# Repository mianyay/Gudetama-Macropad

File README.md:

# Gudetama-Macropad
A Gudetama-themed macropad designed using the Hackpad guide. It has 5 keys with a knob that adjusts the volume, an OLED Display, and 4 RGB LEDs.

Project: https://stardance.hackclub.com/projects/28602

## Features 
- 5x Keys
- 1x Rotary Encoder
- 1x 0.91" SSD1306 OLED, 128x32
- 4x SK6812 MINI-E rear-mount RGB LEDs
- 1x Transparent Acrylic (62mm x 34mm)
- Gudetama-themed silkscreen + engraved case!

## Key Map
| Type | Action |
| --- | --- |
| SW1 | Copy |
| SW2 | Paste |
| SW3 | Undo |
| SW4 | Redo |
| SW5 | Play/Pause |
| Knob (when pressed) | Mute |
| Knob (turned) | Volume adjusted up and down |

## Hardware
- **Microcontroller**: Seeed XIAO RP2040
- **PCB**: 80 x 115 mm, 2-layer, designed in KiCad
- **Case**: 3D-printed tray and frame, designed in Onshape
- **Transparent Window**: 3 mm clear acrylic (laser-cut)

## Firmware

Written in VS Code using CircuitPython + KMK. AI was used to help write some of the code.
- code.py - full firmware
- test_keys.py - buttons only to test wiring

## Repository Layout
- `/pcb` - KiCad schematic, PCB layout, and gerbers
- `/case` - STL files for the top frame, tray and knob
- `/firmware` - CircuitPython/KMK code

## Schematic

## PCB

## CAD

Link: https://cad.onshape.com/documents/9705477a2f20afdacdcfdba6/w/f3cf2669e06390f3bc4361ff/e/a85cb6eed9ad57064a269f1d?renderMode=0&uiState=6ad9a16c61fea2212d106cef

## BOM
- 1x Seeed XIAO RP2040
- 5x Cherry MX switches 
- 5x DSA blank keycaps
- 1x EC11E rotary encoder 
- 4x SK6812 MINI-E RGB LEDs 
- 1x 0.91" SSD1306 OLED display, 128x32
- 6x M3x16mm SHCS bolts
- 6x M3x5mx4mm heatset inserts
- 1x PCB (80 x 115 mm)
- 3x 3D-printed parts (top frame, bottom tray, knob)
- 1x laser-cut part (3 mm clear acrylic window)

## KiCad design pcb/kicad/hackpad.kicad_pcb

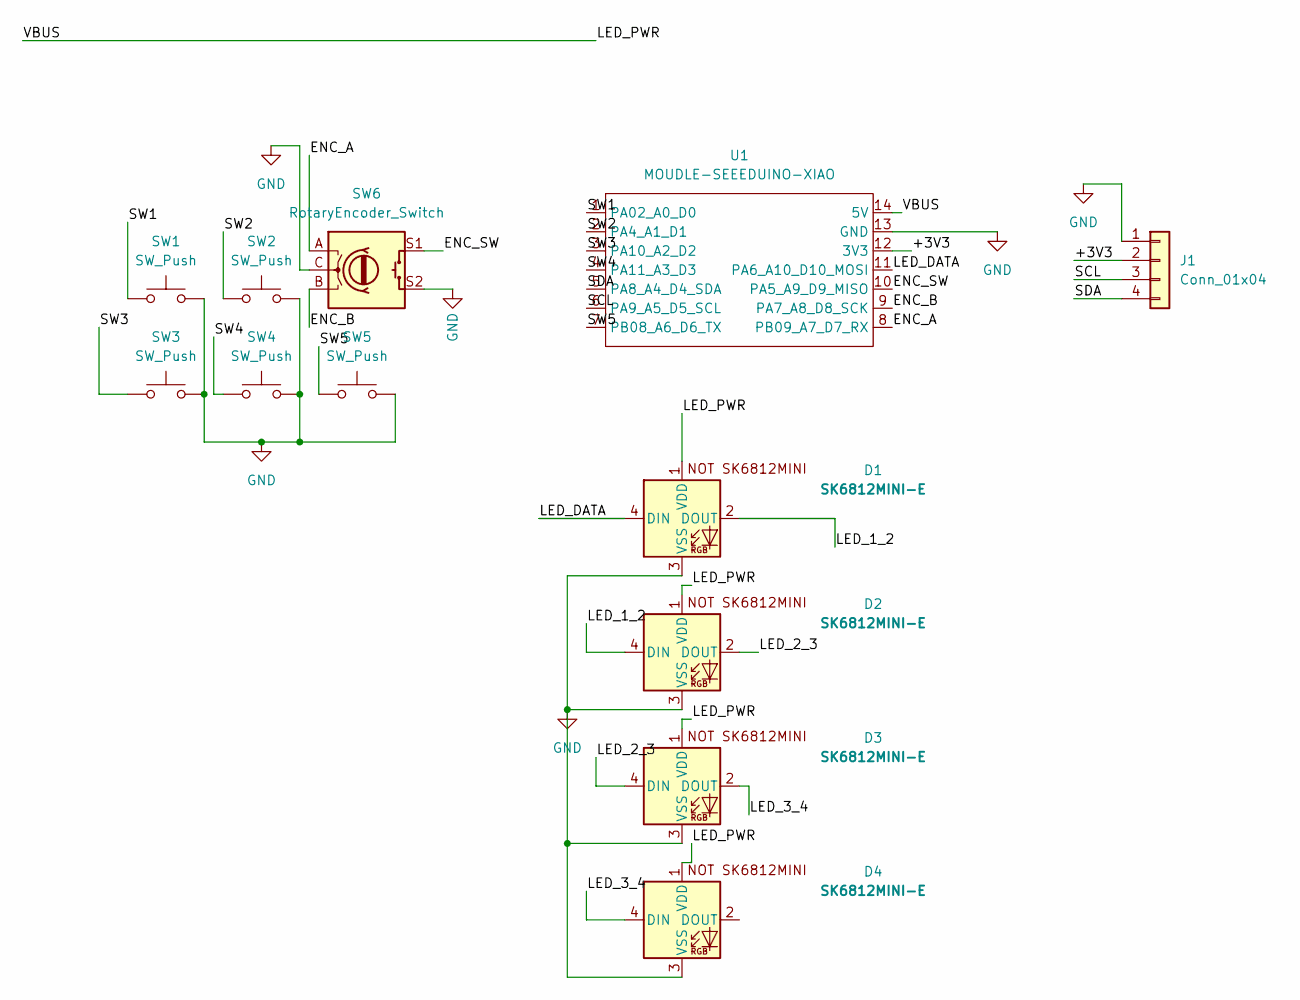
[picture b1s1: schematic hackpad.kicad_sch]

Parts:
D1, D2, D3, D4: SK6812MINI-E; SK6812MINI-E_fixed
J1: Conn_01x04; PinHeader_1x04_P2.54mm_Vertical
SW1, SW2, SW3, SW4, SW5: SW_Push; SW_Cherry_MX_1.00u_PCB
SW6: RotaryEncoder_Switch; RotaryEncoder_Alps_EC11E-Switch_Vertical_H20mm
U1: MOUDLE-SEEEDUINO-XIAO; XIAO-Generic-Hybrid-14P-2.54-21X17.8MM

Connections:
/+3V3: J1.2, U1.12 (3V3)
/ENC_A: SW6.A, U1.8 (PB09_A7_D7_RX)
/ENC_B: SW6.B, U1.9 (PA7_A8_D8_SCK)
/ENC_SW: SW6.S1, U1.10 (PA5_A9_D9_MISO)
/LED_1_2: D1.2 (DOUT), D2.4 (DIN)
/LED_2_3: D2.2 (DOUT), D3.4 (DIN)
/LED_3_4: D3.2 (DOUT), D4.4 (DIN)
/LED_DATA: D1.4 (DIN), U1.11 (PA6_A10_D10_MOSI)
/LED_PWR: D1.1 (VDD), D2.1 (VDD), D3.1 (VDD), D4.1 (VDD), U1.14 (5V)
/SCL: J1.3, U1.6 (PA9_A5_D5_SCL)
/SDA: J1.4, U1.5 (PA8_A4_D4_SDA)
/SW1: SW1.1, U1.1 (PA02_A0_D0)
/SW2: SW2.1, U1.2 (PA4_A1_D1)
/SW3: SW3.1, U1.3 (PA10_A2_D2)
/SW4: SW4.1, U1.4 (PA11_A3_D3)
/SW5: SW5.1, U1.7 (PB08_A6_D6_TX)
GND: D1.3 (VSS), D2.3 (VSS), D3.3 (VSS), D4.3 (VSS), J1.1, SW1.2, SW2.2, SW3.2, SW4.2, SW5.2, SW6.C, SW6.S2, U1.13 (GND)

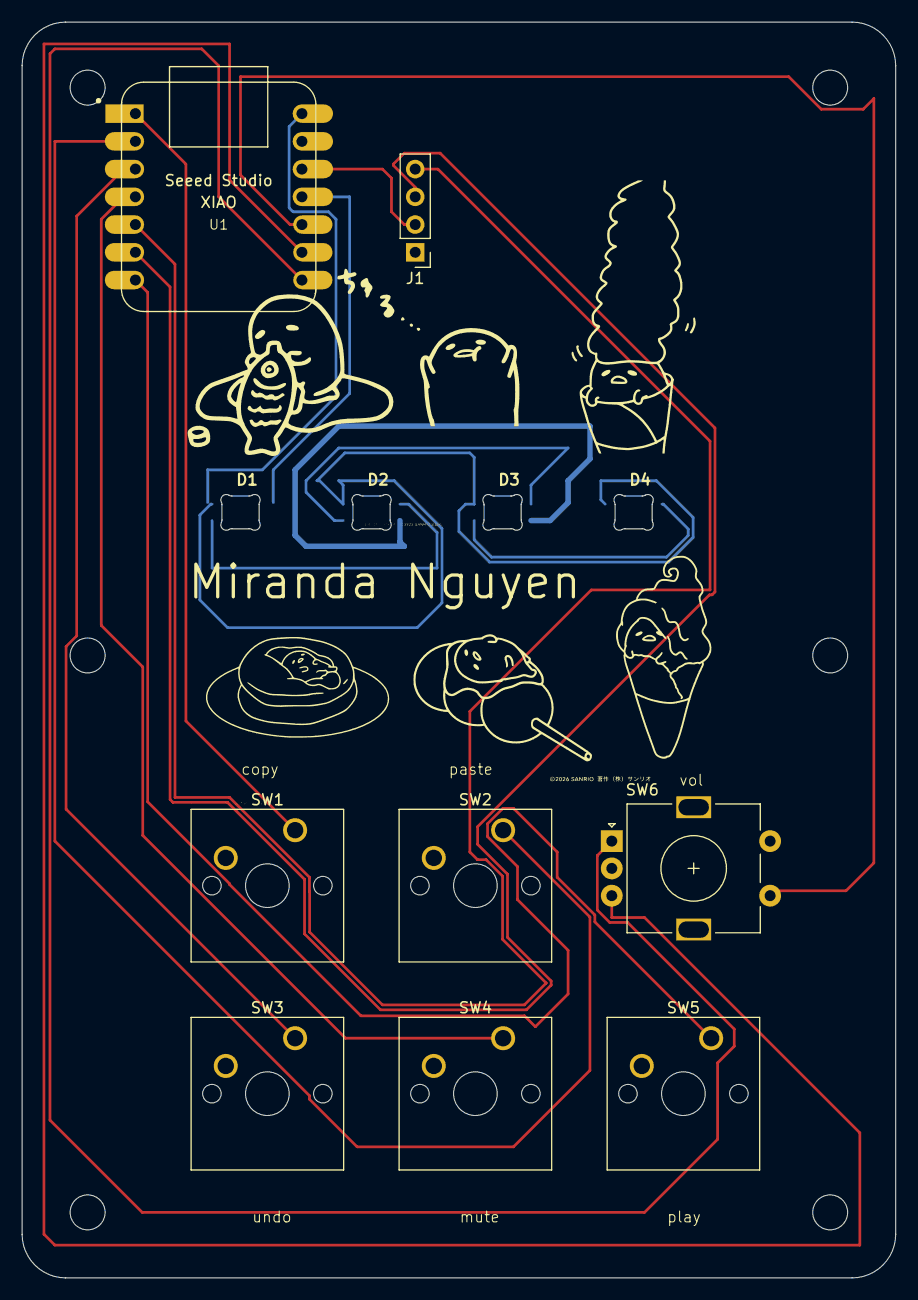
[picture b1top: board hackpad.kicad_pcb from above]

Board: 2 copper layers, 80.0 x 115.0 mm, 12 parts (0 on the bottom side), 17 nets.
